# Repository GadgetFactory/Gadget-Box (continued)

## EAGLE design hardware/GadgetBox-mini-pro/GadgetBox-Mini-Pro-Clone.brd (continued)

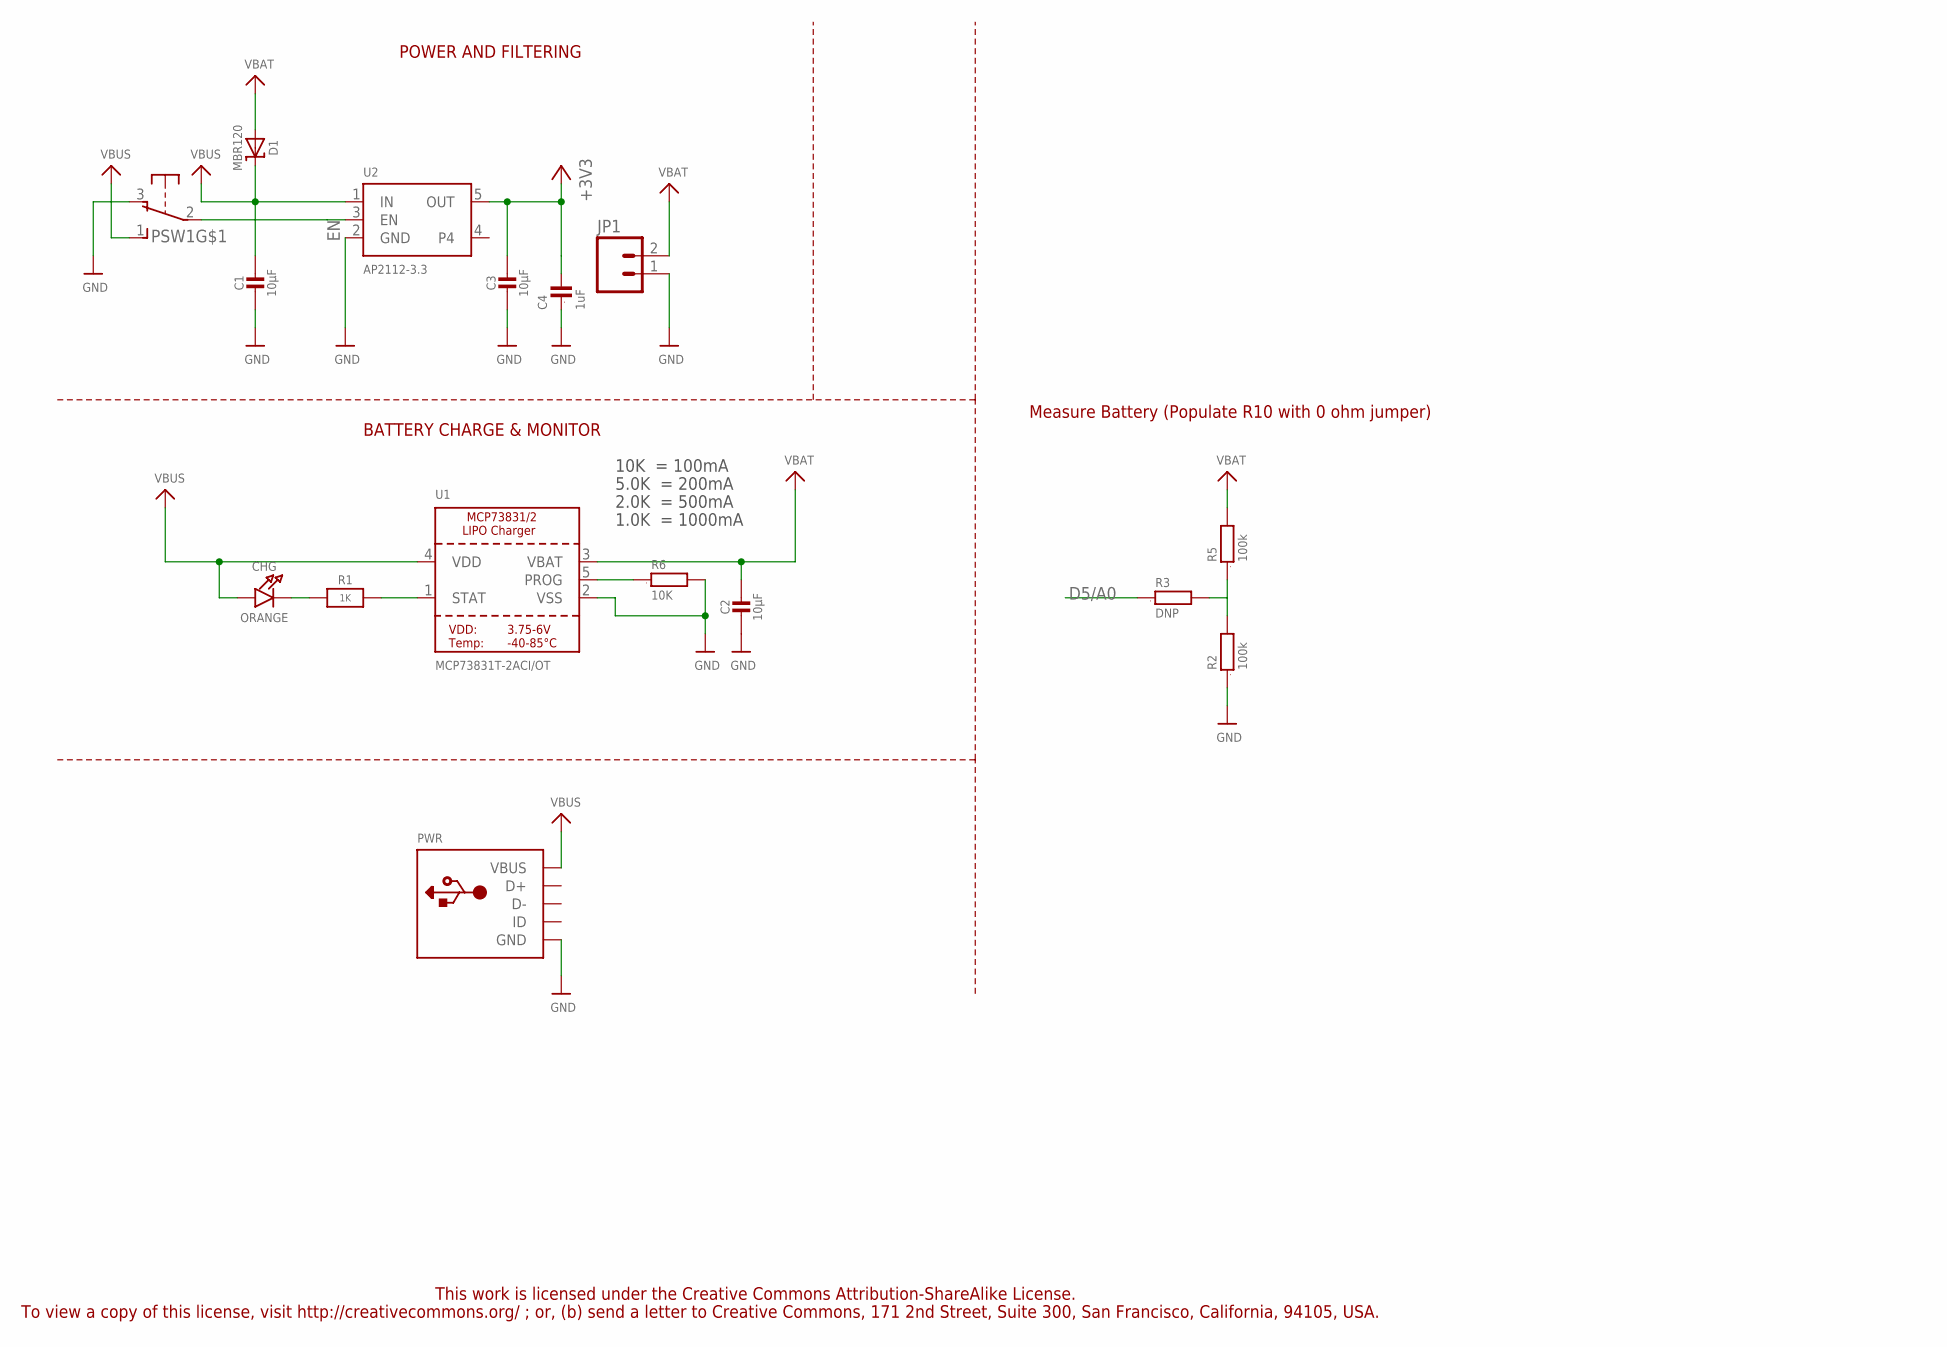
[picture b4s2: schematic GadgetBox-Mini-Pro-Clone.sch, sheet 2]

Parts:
C1, C2, C3: 10µF; 0805-NO; PARTNO CL21F106ZPFNNNE,Samsung,DK,1276-3012-1-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
C4: 1uF; 0603; PARTNO C1608X5R1A105K080AC,TDK CORPORATION (VA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
CHG: ORANGE; CHIPLED_0805_NOOUTLINE; PARTNO LTST-C171EKT,LITE-ON INC (VA),DK,160-14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
D1: MBR120; SOD-123; PARTNO MBR120VLSFT3G,on semiconductor,dk,MBR12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
JP1: M02-JST-2-PTH-NO_SILK; JST-2-PTH-NS; PARTNO B2B-PH-SM4-TB(LF)(SN),JST SALES AMERICA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
PSW1: OS102011MA1Q; PARTNO OS102011MA1QN1,C&K Components,dk,CKN955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
PWR: USBMINIB; USB-MINIB; PARTNO USB-M26FTR,On Shore Technology Inc,DK,E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
R1: 1K; 0603-NO; PARTNO RC0603JR-071KL,YAGEO (VA),dk,311-1.0KGR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
R2, R5: 100k; 0603; PARTNO RC0603JR-07100KL,YAGEO (VA),dk,311-100K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
R3: DNP; 0603
R6: 10K; 0603; PARTNO RC0603JR-0710KL,YAGEO (VA),dk,311-10KGR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
U1: MCP73831T-2ACI/OT; SOT23-5; PARTNO MCP73831T-2ACI/OT,MICROCHIP TECHNOLOGY 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
U2: AP2112-3.3; SOT23-5; PARTNO AP2112K-3.3TRG1,Diodes Incorporated,dk,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

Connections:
3V3: C3.1, C4.2, U2.5 (OUT); also elsewhere on the board
5V0: C1.1, CHG.A, D1.C, PSW1.1 (S), PWR.VBUS, U1.4 (VDD), U2.1 (IN); also elsewhere on the board
D5/A0: R3.1; also elsewhere on the board
EN: PSW1.2, U2.3 (EN)
GND: C1.2, C2.2, C3.2, C4.1, JP1.1, PSW1.3 (O), PWR.GND, R2.1, R6.2, U1.2 (VSS), U2.2 (GND); also elsewhere on the board
unnamed: CHG.C, R1.1
unnamed: R2.2, R3.2, R5.1
unnamed: R1.2, U1.1 (STAT)
unnamed: R6.1, U1.5 (PROG)
VBAT: C2.1, D1.A, JP1.2, R5.2, U1.3 (VBAT)

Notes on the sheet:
POWER AND FILTERING
10K = 100mA
5.0K = 200mA
2.0K = 500mA
1.0K = 1000mA
BATTERY CHARGE & MONITOR
Measure Battery (Populate R10 with 0 ohm jumper)
This work is licensed under the Creative Commons Attribution-ShareAlike License.
To view a copy of this license, visit http://creativecommons.org/ ; or, (b) send a letter to Creative Commons, 171 2nd Street, Suite 300, San Francisco, California, 94105, USA.

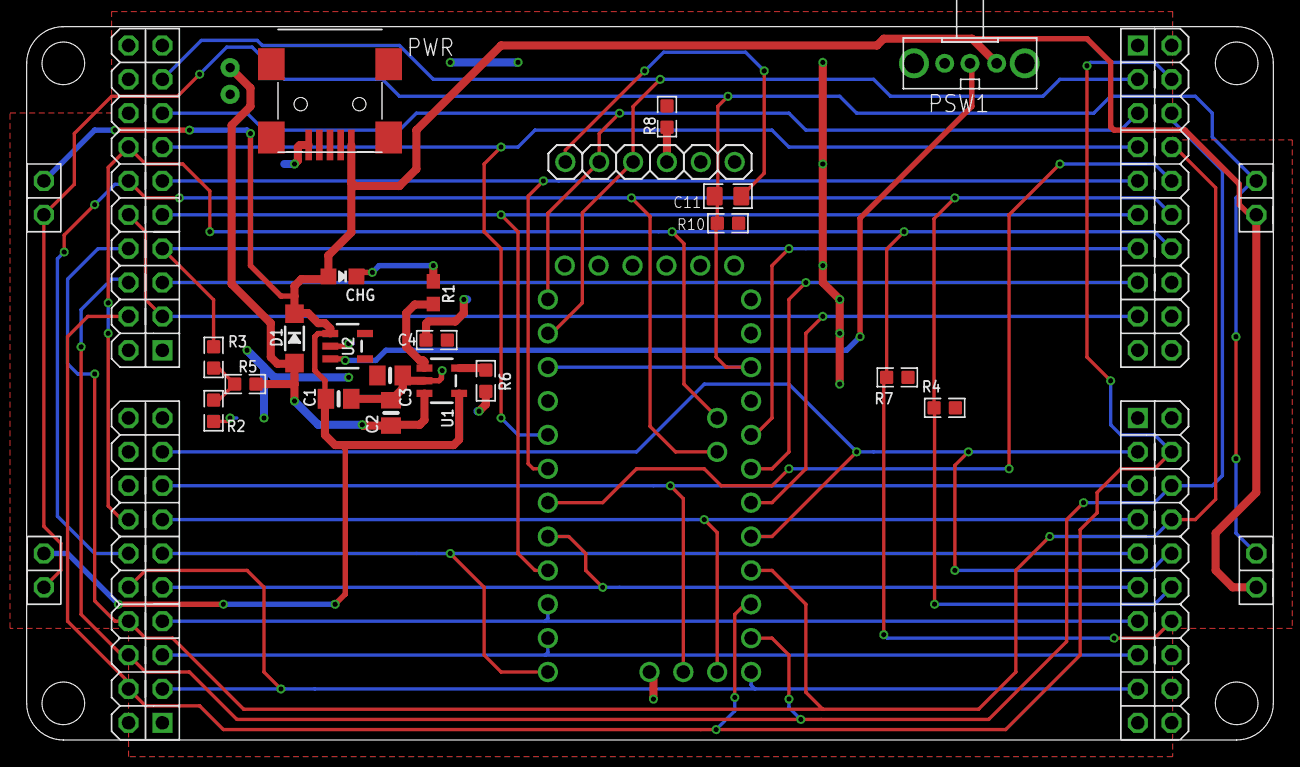
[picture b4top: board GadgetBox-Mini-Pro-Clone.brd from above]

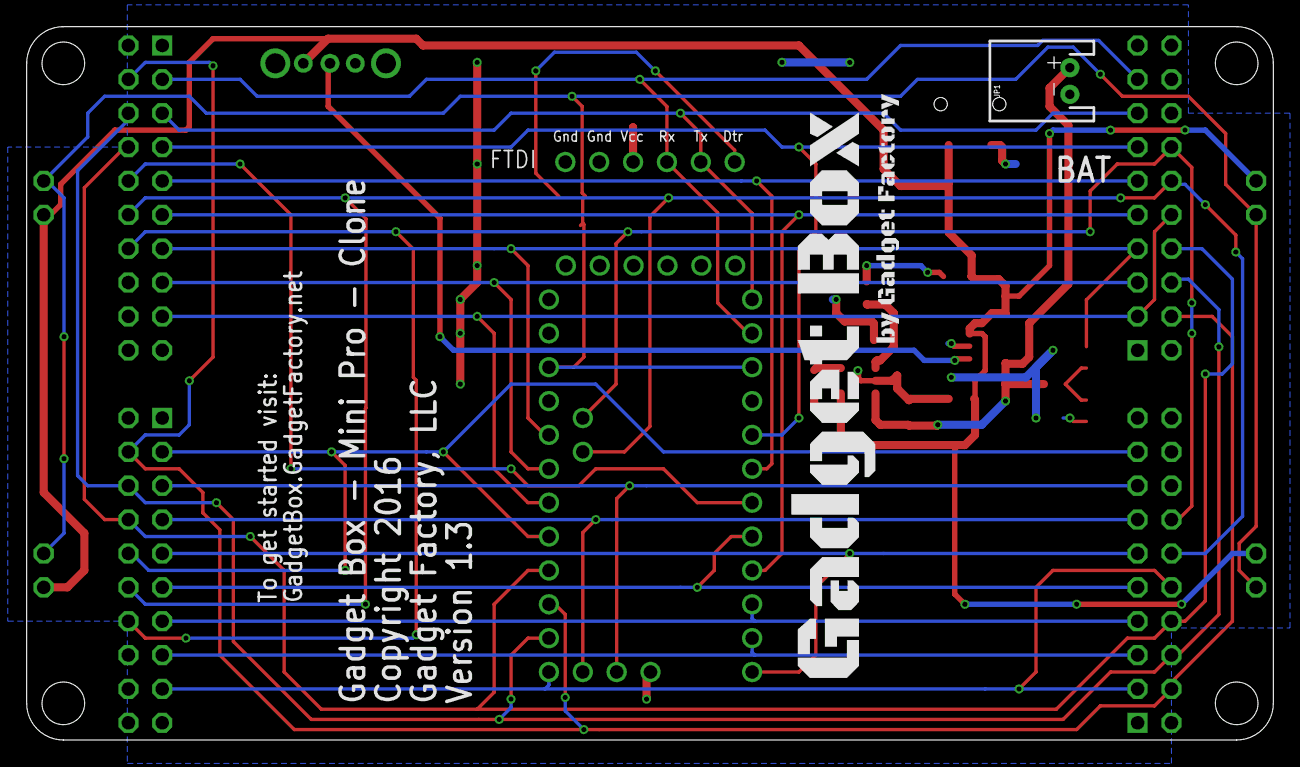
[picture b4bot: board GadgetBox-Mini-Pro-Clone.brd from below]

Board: 2 copper layers, 93.5 x 53.5 mm, 29 parts (2 on the bottom side), 34 nets.

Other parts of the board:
$$U$1: ECOG93P53P5
U$100: GADGETBOX_TEXT

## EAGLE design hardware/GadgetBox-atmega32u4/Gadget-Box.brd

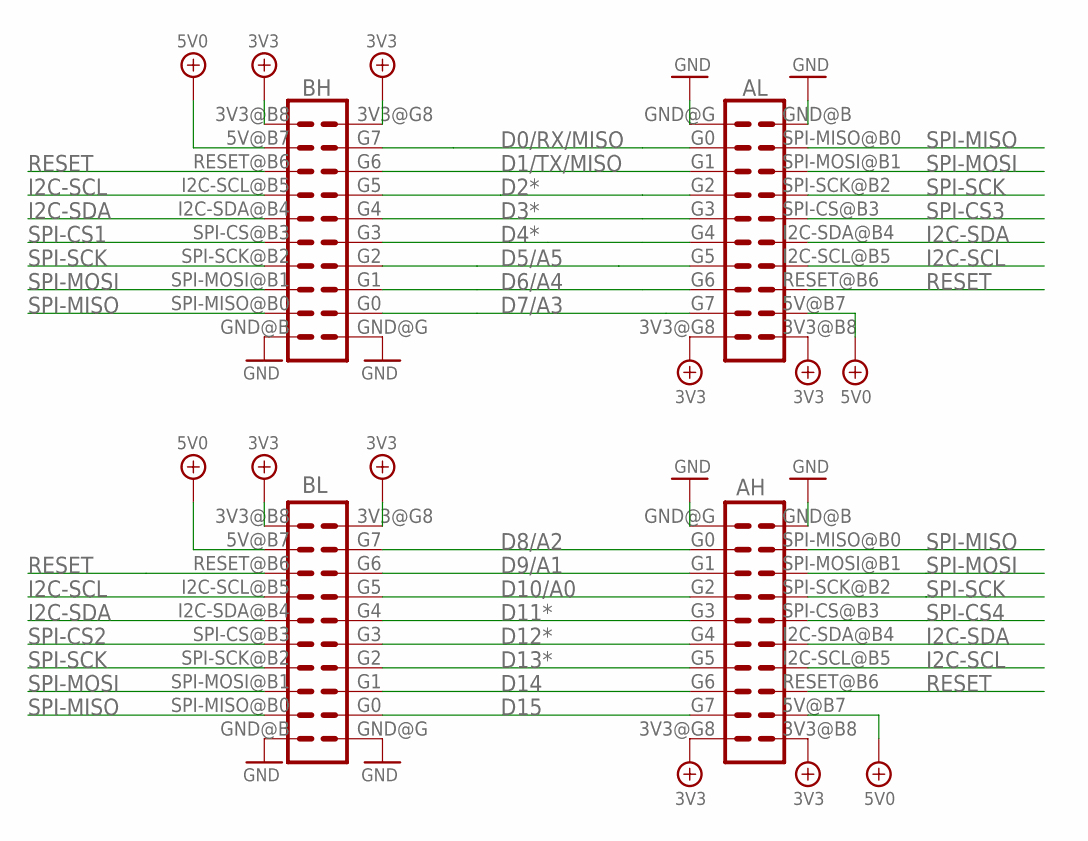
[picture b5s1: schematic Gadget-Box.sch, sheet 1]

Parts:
AH: ECOGECOG_SLOT; ECOG; PARTNO PPPC102LFBN-RC,SULLINS CONNECTOR SOLUTI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
AL: ECOGECOG_SLOT; ECOG; PARTNO PPPC102LFBN-RC,SULLINS CONNECTOR SOLUTI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
BH: ECOGECOG_SLOT; ECOG; PARTNO PPPC102LFBN-RC,SULLINS CONNECTOR SOLUTI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
BL: ECOGECOG_SLOT; ECOG; PARTNO PPPC102LFBN-RC,SULLINS CONNECTOR SOLUTI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

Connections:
3V3: AH.3V3@B8 (3V3), AH.3V3@G8 (3V3), AL.3V3@B8 (3V3), AL.3V3@G8 (3V3), BH.3V3@B8 (3V3), BH.3V3@G8 (3V3), BL.3V3@B8 (3V3), BL.3V3@G8 (3V3); also elsewhere on the board
D0/RX/MISO: AL.G0, BH.G7; also elsewhere on the board
D1/TX/MISO: AL.G1, BH.G6; also elsewhere on the board
D2*: AL.G2, BH.G5; also elsewhere on the board
D3*: AL.G3, BH.G4; also elsewhere on the board
D4*: AL.G4, BH.G3; also elsewhere on the board
D5/A5: AL.G5, BH.G2; also elsewhere on the board
D6/A4: AL.G6, BH.G1; also elsewhere on the board
D7/A3: AL.G7, BH.G0; also elsewhere on the board
D8/A2: AH.G0, BL.G7; also elsewhere on the board
D9/A1: AH.G1, BL.G6; also elsewhere on the board
D10/A0: AH.G2, BL.G5; also elsewhere on the board
D11*: AH.G3, BL.G4; also elsewhere on the board
D12*: AH.G4, BL.G3; also elsewhere on the board
D13*: AH.G5, BL.G2; also elsewhere on the board
D14: AH.G6, BL.G1; also elsewhere on the board
D15: AH.G7, BL.G0; also elsewhere on the board
GND: AH.GND@B (GND), AH.GND@G (GND), AL.GND@B (GND), AL.GND@G (GND), BH.GND@B (GND), BH.GND@G (GND), BL.GND@B (GND), BL.GND@G (GND); also elsewhere on the board
I2C-SCL: AH.I2C-SCL@B5 (I2C-SCL), AL.I2C-SCL@B5 (I2C-SCL), BH.I2C-SCL@B5 (I2C-SCL), BL.I2C-SCL@B5 (I2C-SCL); also elsewhere on the board
I2C-SDA: AH.I2C-SDA@B4 (I2C-SDA), AL.I2C-SDA@B4 (I2C-SDA), BH.I2C-SDA@B4 (I2C-SDA), BL.I2C-SDA@B4 (I2C-SDA); also elsewhere on the board
RESET: AH.RESET@B6 (RESET), AL.RESET@B6 (RESET), BH.RESET@B6 (RESET), BL.RESET@B6 (RESET); also elsewhere on the board
SPI-CS1: BH.SPI-CS@B3 (SPI-CS); also elsewhere on the board
SPI-CS2: BL.SPI-CS@B3 (SPI-CS); also elsewhere on the board
SPI-CS3: AL.SPI-CS@B3 (SPI-CS); also elsewhere on the board
SPI-CS4: AH.SPI-CS@B3 (SPI-CS); also elsewhere on the board
SPI-MISO: AH.SPI-MISO@B0 (SPI-MISO), AL.SPI-MISO@B0 (SPI-MISO), BH.SPI-MISO@B0 (SPI-MISO), BL.SPI-MISO@B0 (SPI-MISO); also elsewhere on the board
SPI-MOSI: AH.SPI-MOSI@B1 (SPI-MOSI), AL.SPI-MOSI@B1 (SPI-MOSI), BH.SPI-MOSI@B1 (SPI-MOSI), BL.SPI-MOSI@B1 (SPI-MOSI); also elsewhere on the board
SPI-SCK: AH.SPI-SCK@B2 (SPI-SCK), AL.SPI-SCK@B2 (SPI-SCK), BH.SPI-SCK@B2 (SPI-SCK), BL.SPI-SCK@B2 (SPI-SCK); also elsewhere on the board
VBUS: AH.5V@B7 (5V), AL.5V@B7 (5V), BH.5V@B7 (5V), BL.5V@B7 (5V); also elsewhere on the board

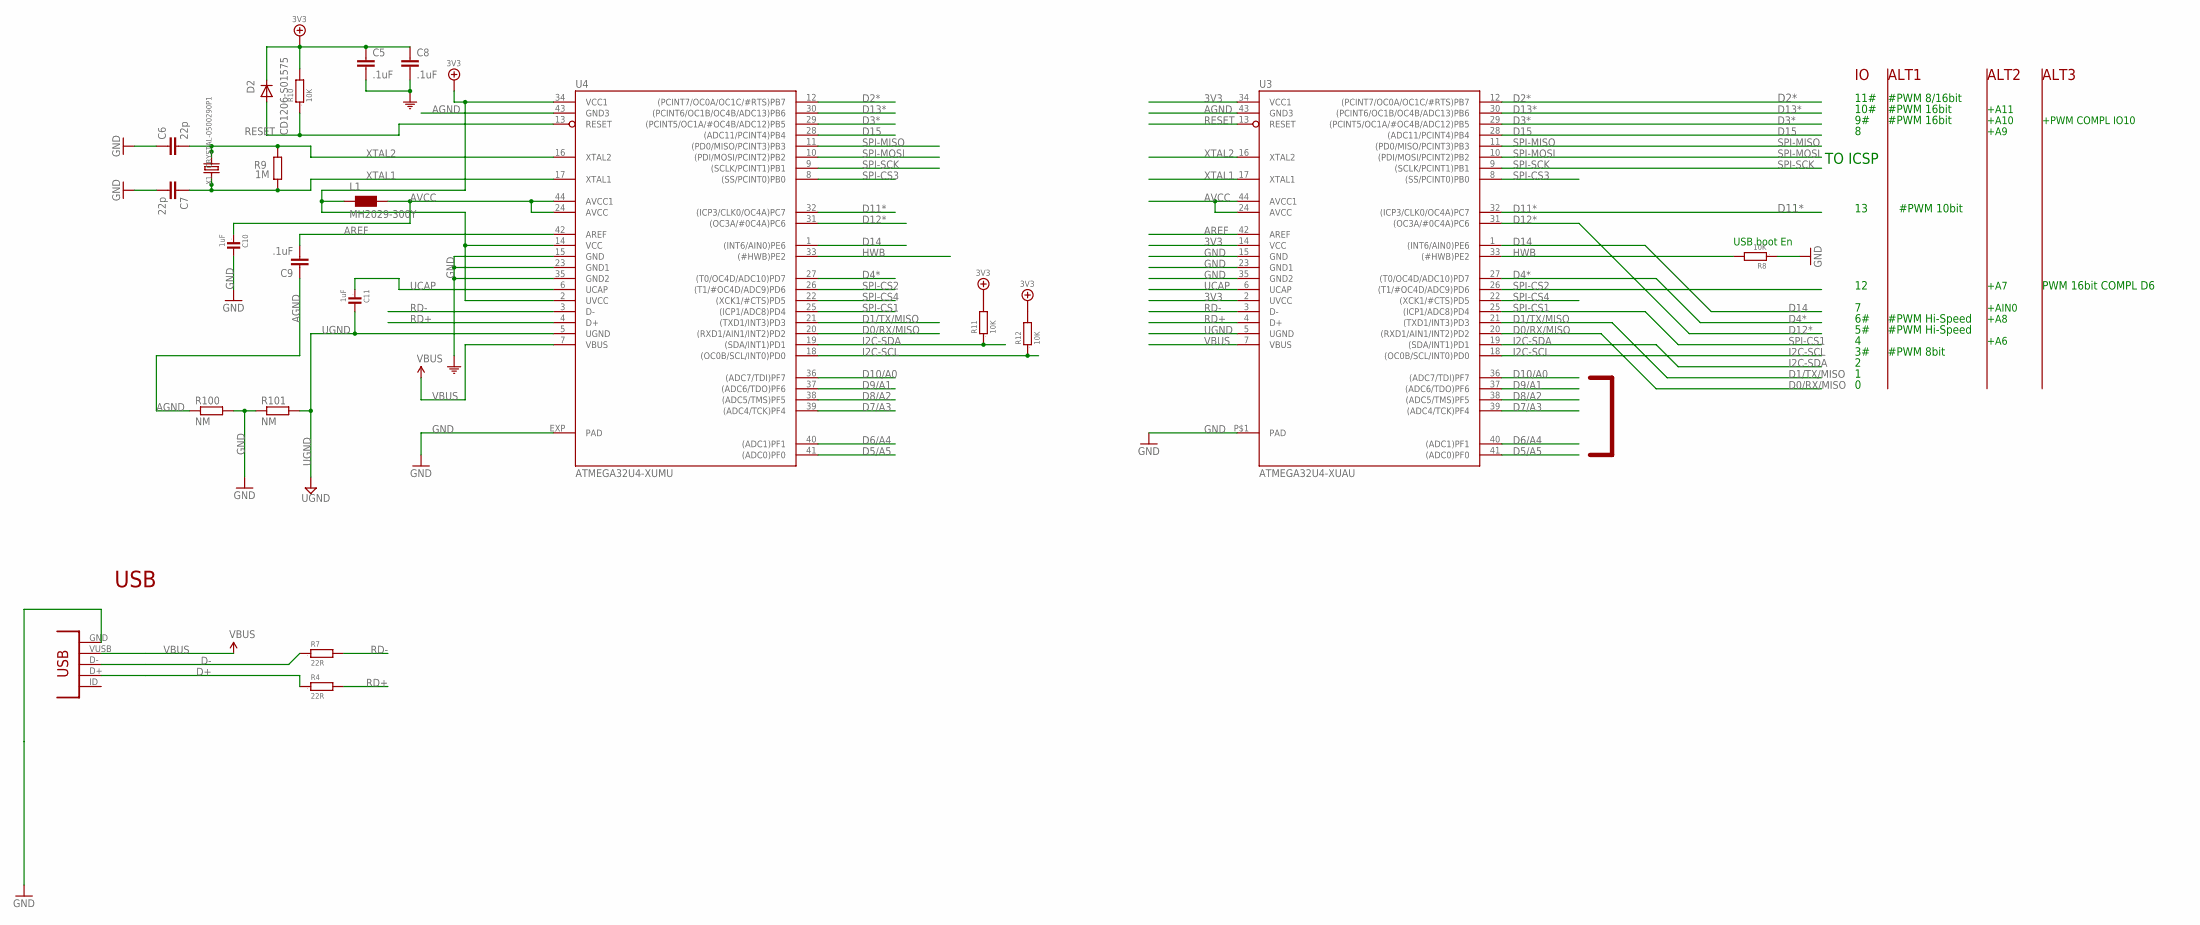
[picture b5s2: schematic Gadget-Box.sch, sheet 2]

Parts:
C5, C8, C9: .1uF; C0603-ROUND; PARTNO GRM188F51E104ZA01D,MURATA ELECTRONICS (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
C6, C7: 22p; C0603-ROUND; PARTNO C1608C0G1H220J080AA,TDK CORPORATION (VA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
C10, C11: 1uF; 0603; PARTNO C1608X5R1A105K080AC,TDK CORPORATION (VA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
D2: CD1206-S01575; MINIMELF; PARTNO CD1206-S01575,BOURNS INC (VA),dk,CD1206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
L1: MH2029-300Y; 0805; PARTNO MH2029-300Y,BOURNS INC (VA),dk,MH2029-3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
R4, R7: 22R; 0805; PARTNO RMCF0805JT22R0,STACKPOLE ELECTRONICS IN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
R8, R10, R11, R12: 10K; 0603; PARTNO RC0603JR-0710KL,YAGEO (VA),dk,311-10KGR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
R9: 1M; R0603-ROUND; PARTNO RMCF0603JT1M00,STACKPOLE ELECTRONICS IN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
R100, R101: NM; R0402
U3: ATMEGA32U4-XUAU; TQFP44-PAD; PARTNO ATMEGA32U4-AUR,ATMEL (VA),dk,ATMEGA32U4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
U4: ATMEGA32U4-XUMU; QFN44ML7X7
USB: CONN_USB; CONN_USB_MINI-B; PARTNO USB-M26FTR,ON SHORE TECHNOLOGY INC (VA)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
X1: CRYSTAL-0500290P1; 2P-SMD-5.0X3.2; PARTNO ABM3-8.000MHZ-D2Y-T,Abracon Corporation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

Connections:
3V3: C5.1, C8.1, D2.C, L1.1, R10.2, R11.2, R12.2, U3.2 (UVCC), U3.14 (VCC), U3.34 (VCC1), U4.2 (UVCC), U4.14 (VCC), U4.34 (VCC1); also elsewhere on the board
AGND: C9.1, R100.1, U3.43 (GND3), U4.43 (GND3)
AREF: C9.2, U3.42 (AREF), U4.42 (AREF)
AVCC: C10.1, L1.2, U3.24 (AVCC), U3.44 (AVCC1), U4.24 (AVCC), U4.44 (AVCC1)
D0/RX/MISO: U3.20 ((RXD1/AIN1/INT2)PD2), U4.20 ((RXD1/AIN1/INT2)PD2); also elsewhere on the board
D1/TX/MISO: U3.21 ((TXD1/INT3)PD3), U4.21 ((TXD1/INT3)PD3); also elsewhere on the board
D2*: U3.12 ((PCINT7/OC0A/OC1C/#RTS)PB7), U4.12 ((PCINT7/OC0A/OC1C/#RTS)PB7); also elsewhere on the board
D3*: U3.29 ((PCINT5/OC1A/#OC4B/ADC12)PB5), U4.29 ((PCINT5/OC1A/#OC4B/ADC12)PB5); also elsewhere on the board
D4*: U3.27 ((T0/OC4D/ADC10)PD7), U4.27 ((T0/OC4D/ADC10)PD7); also elsewhere on the board
D5/A5: U3.41 ((ADC0)PF0), U4.41 ((ADC0)PF0); also elsewhere on the board
D6/A4: U3.40 ((ADC1)PF1), U4.40 ((ADC1)PF1); also elsewhere on the board
D7/A3: U3.39 ((ADC4/TCK)PF4), U4.39 ((ADC4/TCK)PF4); also elsewhere on the board
D8/A2: U3.38 ((ADC5/TMS)PF5), U4.38 ((ADC5/TMS)PF5); also elsewhere on the board
D9/A1: U3.37 ((ADC6/TDO)PF6), U4.37 ((ADC6/TDO)PF6); also elsewhere on the board
D10/A0: U3.36 ((ADC7/TDI)PF7), U4.36 ((ADC7/TDI)PF7); also elsewhere on the board
D11*: U3.32 ((ICP3/CLK0/OC4A)PC7), U4.32 ((ICP3/CLK0/OC4A)PC7); also elsewhere on the board
D12*: U3.31 ((OC3A/#0C4A)PC6), U4.31 ((OC3A/#0C4A)PC6); also elsewhere on the board
D13*: U3.30 ((PCINT6/OC1B/OC4B/ADC13)PB6), U4.30 ((PCINT6/OC1B/OC4B/ADC13)PB6); also elsewhere on the board
D14: U3.1 ((INT6/AIN0)PE6), U4.1 ((INT6/AIN0)PE6); also elsewhere on the board
D15: U3.28 ((ADC11/PCINT4)PB4), U4.28 ((ADC11/PCINT4)PB4); also elsewhere on the board
D+: R4.1, USB.D+
D-: R7.1, USB.D-
GND: C5.2, C6.1, C7.2, C8.2, C10.2, R8.1, R100.2, R101.1, U3.15 (GND), U3.23 (GND1), U3.35 (GND2), U3.P$1 (PAD), U4.15 (GND), U4.23 (GND1), U4.35 (GND2), U4.EXP (PAD), USB.GND; also elsewhere on the board
HWB: R8.2, U3.33 ((#HWB)PE2), U4.33 ((#HWB)PE2)
I2C-SCL: R12.1, U3.18 ((OC0B/SCL/INT0)PD0), U4.18 ((OC0B/SCL/INT0)PD0); also elsewhere on the board
I2C-SDA: R11.1, U3.19 ((SDA/INT1)PD1), U4.19 ((SDA/INT1)PD1); also elsewhere on the board
RD+: R4.2, U3.4 (D+), U4.4 (D+)
RD-: R7.2, U3.3 (D-), U4.3 (D-)
RESET: D2.A, R10.1, U3.13 (RESET), U4.13 (RESET); also elsewhere on the board
SPI-CS1: U3.25 ((ICP1/ADC8)PD4), U4.25 ((ICP1/ADC8)PD4); also elsewhere on the board
SPI-CS2: U3.26 ((T1/#OC4D/ADC9)PD6), U4.26 ((T1/#OC4D/ADC9)PD6); also elsewhere on the board
SPI-CS3: U3.8 ((SS/PCINT0)PB0), U4.8 ((SS/PCINT0)PB0); also elsewhere on the board
SPI-CS4: U3.22 ((XCK1/#CTS)PD5), U4.22 ((XCK1/#CTS)PD5); also elsewhere on the board
SPI-MISO: U3.11 ((PD0/MISO/PCINT3)PB3), U4.11 ((PD0/MISO/PCINT3)PB3); also elsewhere on the board
SPI-MOSI: U3.10 ((PDI/MOSI/PCINT2)PB2), U4.10 ((PDI/MOSI/PCINT2)PB2); also elsewhere on the board
SPI-SCK: U3.9 ((SCLK/PCINT1)PB1), U4.9 ((SCLK/PCINT1)PB1); also elsewhere on the board
UCAP: C11.1, U3.6 (UCAP), U4.6 (UCAP)
UGND: C11.2, R101.2, U3.5 (UGND), U4.5 (UGND)
VBUS: U3.7 (VBUS), U4.7 (VBUS), USB.VUSB; also elsewhere on the board
XTAL1: C7.1, R9.1, U3.17 (XTAL1), U4.17 (XTAL1), X1.1
XTAL2: C6.2, R9.2, U3.16 (XTAL2), U4.16 (XTAL2), X1.2

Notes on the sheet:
USB boot En
USB
TO ICSP
10#
11#
#PWM 8bit
#PWM Hi-Speed
#PWM 8/16bit
#PWM 16bit
PWM 16bit COMPL D6
#PWM 10bit
+A6
+A7
+A11
+A10
+A8
+A9
+PWM COMPL IO10
+AIN0
ALT1
ALT2
ALT3

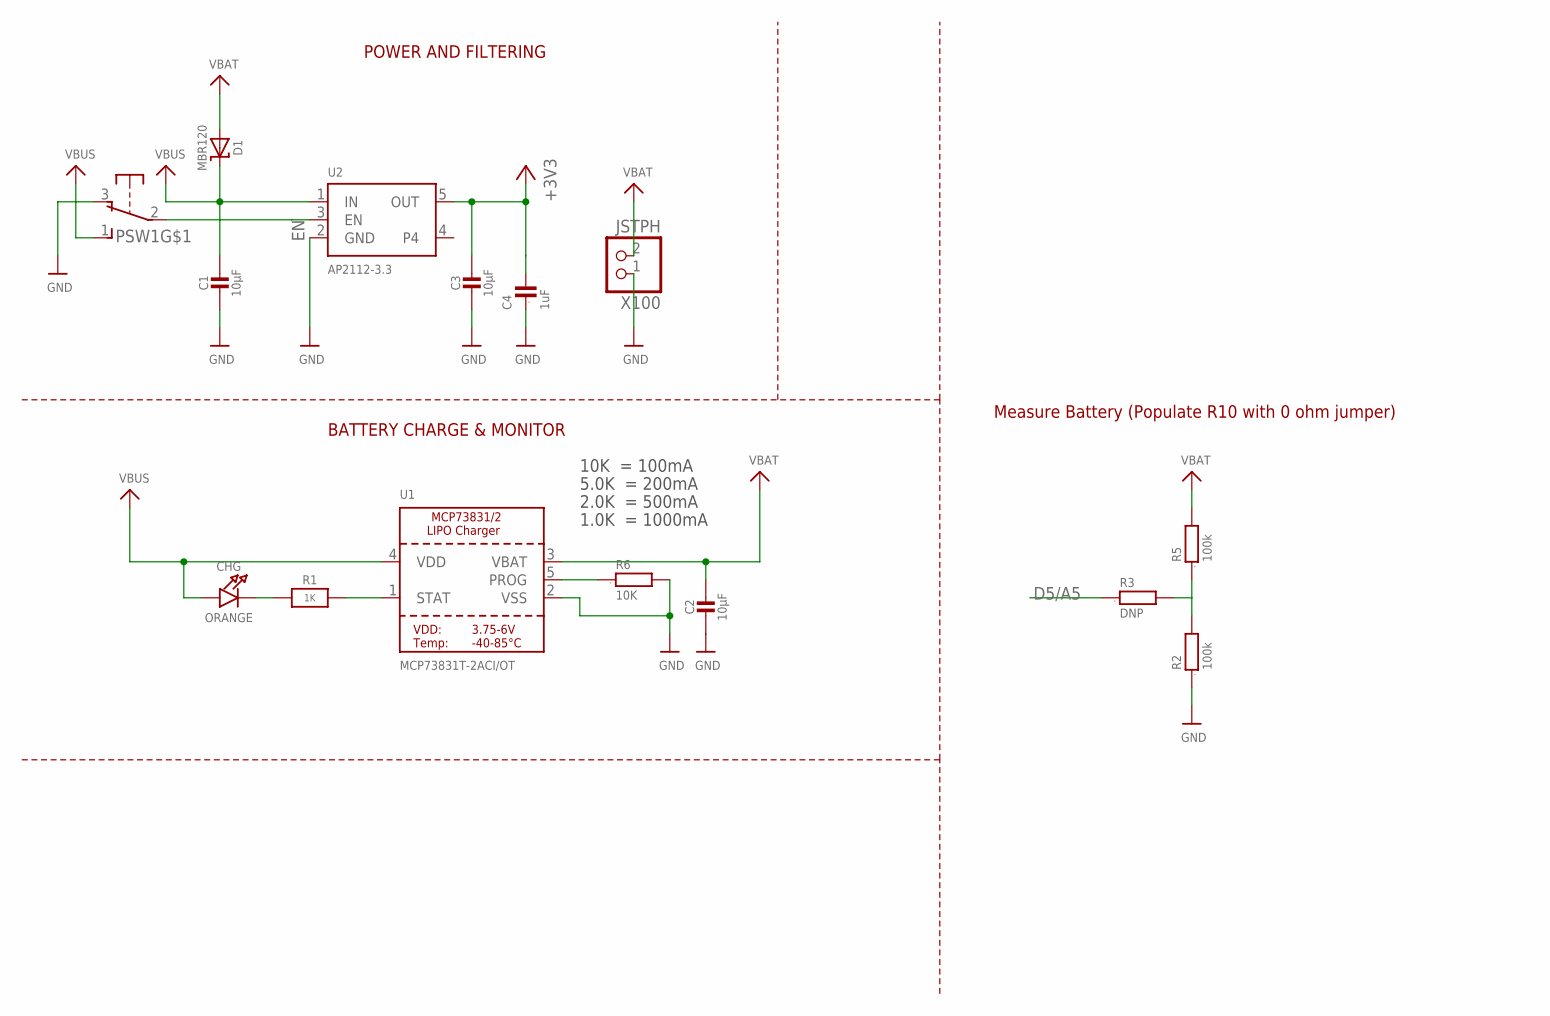
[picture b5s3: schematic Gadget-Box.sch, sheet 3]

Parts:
C1, C2, C3: 10µF; 0805-NO; PARTNO CL21F106ZPFNNNE,Samsung,DK,1276-3012-1-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
C4: 1uF; 0603; PARTNO C1608X5R1A105K080AC,TDK CORPORATION (VA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
CHG: ORANGE; CHIPLED_0805_NOOUTLINE; PARTNO LTST-C171EKT,LITE-ON INC (VA),DK,160-14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
D1: MBR120; SOD-123; PARTNO MBR120VLSFT3G,on semiconductor,dk,MBR12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
PSW1: OS102011MA1Q; PARTNO OS102011MA1QN1,C&K Components,dk,CKN955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
R1: 1K; 0603-NO; PARTNO RC0603JR-071KL,YAGEO (VA),dk,311-1.0KGR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
R2, R5: 100k; 0603; PARTNO RC0603JR-07100KL,YAGEO (VA),dk,311-100K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
R3: DNP; 0603
R6: 10K; 0603; PARTNO RC0603JR-0710KL,YAGEO (VA),dk,311-10KGR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
U1: MCP73831T-2ACI/OT; SOT23-5; PARTNO MCP73831T-2ACI/OT,MICROCHIP TECHNOLOGY 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
U2: AP2112-3.3; SOT23-5; PARTNO AP2112K-3.3TRG1,Diodes Incorporated,dk,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
X100: JSTPH; JSTPH2; PARTNO S2B-PH-SM4-TB(LF)(SN),JST SALES AMERICA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

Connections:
3V3: C3.1, C4.2, U2.5 (OUT); also elsewhere on the board
D5/A5: R3.1; also elsewhere on the board
EN: PSW1.2, U2.3 (EN)
GND: C1.2, C2.2, C3.2, C4.1, PSW1.3 (O), R2.1, R6.2, U1.2 (VSS), U2.2 (GND), X100.1; also elsewhere on the board
unnamed: CHG.C, R1.1
unnamed: R2.2, R3.2, R5.1
unnamed: R1.2, U1.1 (STAT)
unnamed: R6.1, U1.5 (PROG)
VBAT: C2.1, D1.A, R5.2, U1.3 (VBAT), X100.2
VBUS: C1.1, CHG.A, D1.C, PSW1.1 (S), U1.4 (VDD), U2.1 (IN); also elsewhere on the board

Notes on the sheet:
POWER AND FILTERING
10K = 100mA
5.0K = 200mA
2.0K = 500mA
1.0K = 1000mA
BATTERY CHARGE & MONITOR
Measure Battery (Populate R10 with 0 ohm jumper)

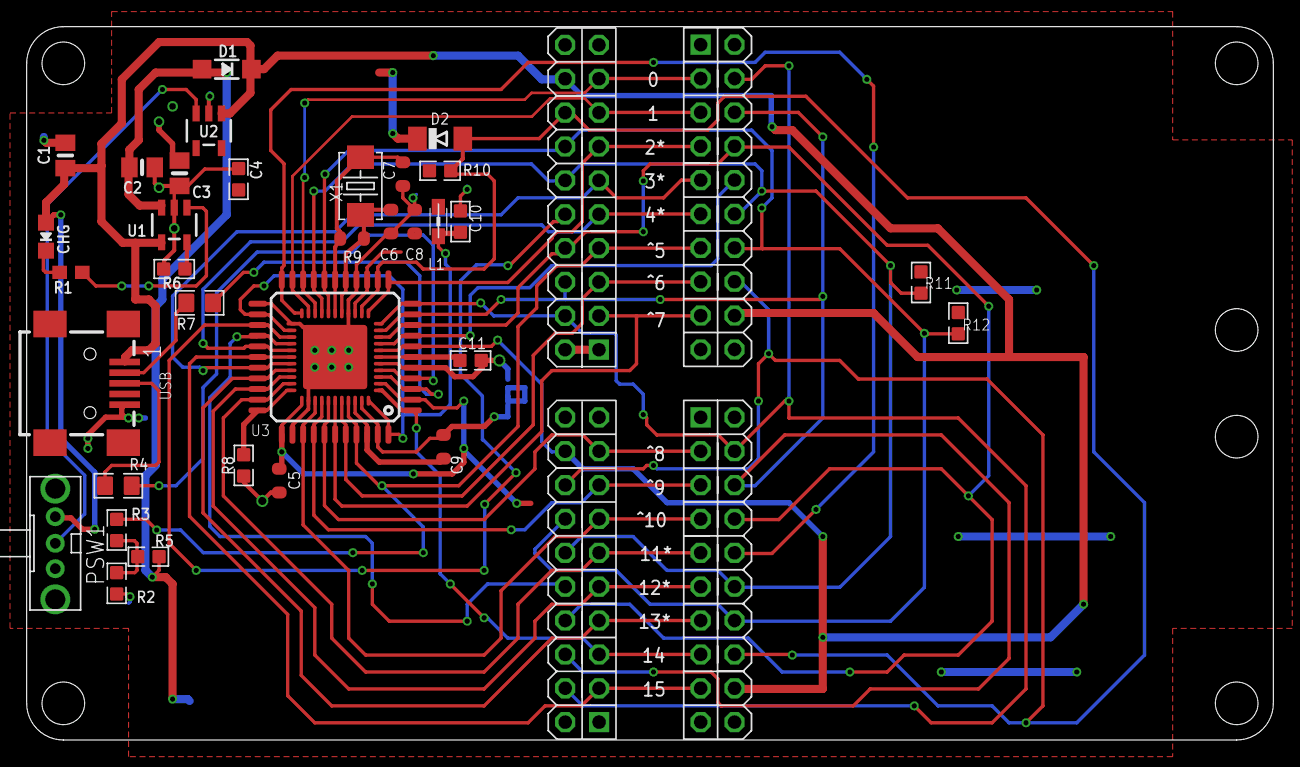
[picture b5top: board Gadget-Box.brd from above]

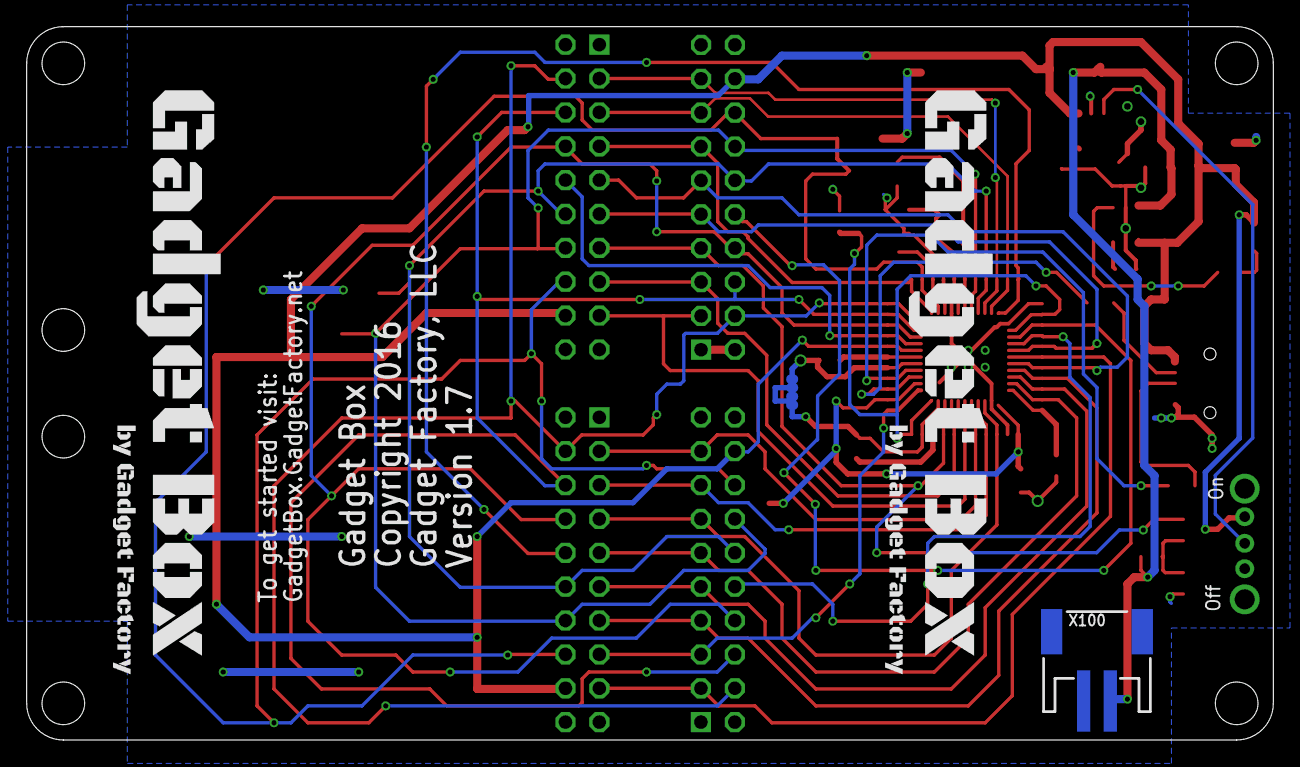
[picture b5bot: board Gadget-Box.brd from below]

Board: 2 copper layers, 93.5 x 53.5 mm, 44 parts (5 on the bottom side), 47 nets.

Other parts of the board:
$$U$1: ECOG93P53P5
U$100, U$101: GADGETBOX_TEXT

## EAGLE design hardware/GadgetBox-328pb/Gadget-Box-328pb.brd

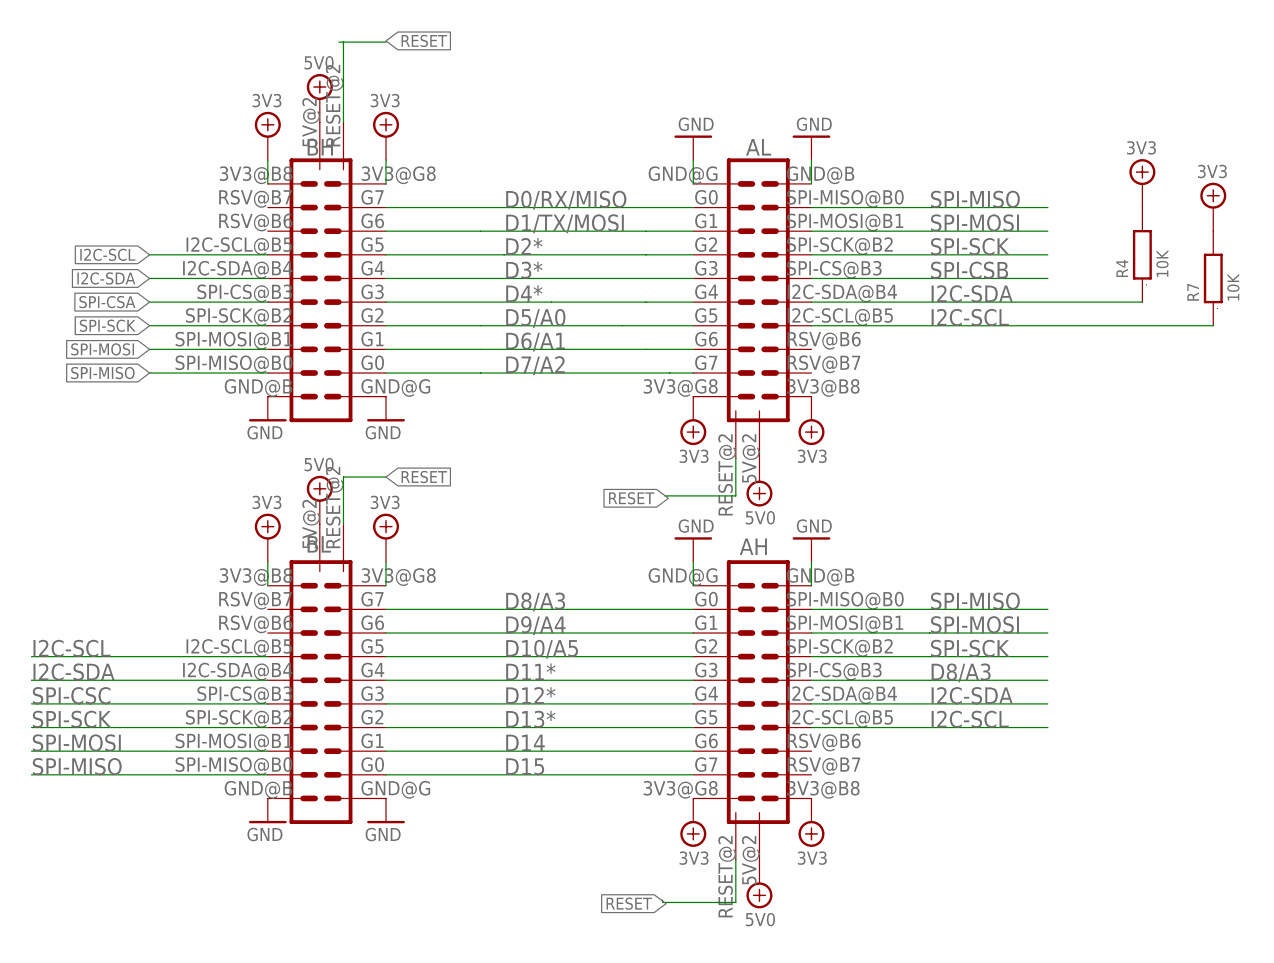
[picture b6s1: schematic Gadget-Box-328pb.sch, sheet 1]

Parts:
AH: ECOGECOG_SLOT_ALT1; ECOG_ALT1; PARTNO PPPC102LFBN-RC,SULLINS CONNECTOR SOLUTI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
AL: ECOGECOG_SLOT_ALT1; ECOG_ALT1; PARTNO PPPC102LFBN-RC,SULLINS CONNECTOR SOLUTI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
BH: ECOGECOG_SLOT_ALT1; ECOG_ALT1; PARTNO PPPC102LFBN-RC,SULLINS CONNECTOR SOLUTI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
BL: ECOGECOG_SLOT_ALT1; ECOG_ALT1; PARTNO PPPC102LFBN-RC,SULLINS CONNECTOR SOLUTI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
R4, R7: 10K; 0603; PARTNO RC0603JR-0710KL,YAGEO (VA),dk,311-10KGR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

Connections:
3V3: AH.3V3@B8 (3V3), AH.3V3@G8 (3V3), AL.3V3@B8 (3V3), AL.3V3@G8 (3V3), BH.3V3@B8 (3V3), BH.3V3@G8 (3V3), BL.3V3@B8 (3V3), BL.3V3@G8 (3V3), R4.2, R7.2; also elsewhere on the board
5V0: AH.5V@2 (5V), AL.5V@2 (5V), BH.5V@2 (5V), BL.5V@2 (5V); also elsewhere on the board
D0/RX/MISO: AL.G0, BH.G7; also elsewhere on the board
D1/TX/MOSI: AL.G1, BH.G6; also elsewhere on the board
D2*: AL.G2, BH.G5; also elsewhere on the board
D3*: AL.G3, BH.G4; also elsewhere on the board
D4*: AL.G4, BH.G3; also elsewhere on the board
D5/A0: AL.G5, BH.G2; also elsewhere on the board
D6/A1: AL.G6, BH.G1; also elsewhere on the board
D7/A2: AL.G7, BH.G0; also elsewhere on the board
D8/A3: AH.G0, AH.SPI-CS@B3 (SPI-CS), BL.G7; also elsewhere on the board
D9/A4: AH.G1, BL.G6; also elsewhere on the board
D10/A5: AH.G2, BL.G5; also elsewhere on the board
D11*: AH.G3, BL.G4; also elsewhere on the board
D12*: AH.G4, BL.G3; also elsewhere on the board
D13*: AH.G5, BL.G2; also elsewhere on the board
D14: AH.G6, BL.G1; also elsewhere on the board
D15: AH.G7, BL.G0; also elsewhere on the board
GND: AH.GND@B (GND), AH.GND@G (GND), AL.GND@B (GND), AL.GND@G (GND), BH.GND@B (GND), BH.GND@G (GND), BL.GND@B (GND), BL.GND@G (GND); also elsewhere on the board
I2C-SCL: AH.I2C-SCL@B5 (I2C-SCL), AL.I2C-SCL@B5 (I2C-SCL), BH.I2C-SCL@B5 (I2C-SCL), BL.I2C-SCL@B5 (I2C-SCL), R7.1; also elsewhere on the board
I2C-SDA: AH.I2C-SDA@B4 (I2C-SDA), AL.I2C-SDA@B4 (I2C-SDA), BH.I2C-SDA@B4 (I2C-SDA), BL.I2C-SDA@B4 (I2C-SDA), R4.1; also elsewhere on the board
RESET: AH.RESET@2 (RESET), AL.RESET@2 (RESET), BH.RESET@2 (RESET), BL.RESET@2 (RESET); also elsewhere on the board
SPI-CSA: BH.SPI-CS@B3 (SPI-CS); also elsewhere on the board
SPI-CSB: AL.SPI-CS@B3 (SPI-CS); also elsewhere on the board
SPI-CSC: BL.SPI-CS@B3 (SPI-CS); also elsewhere on the board
SPI-MISO: AH.SPI-MISO@B0 (SPI-MISO), AL.SPI-MISO@B0 (SPI-MISO), BH.SPI-MISO@B0 (SPI-MISO), BL.SPI-MISO@B0 (SPI-MISO); also elsewhere on the board
SPI-MOSI: AH.SPI-MOSI@B1 (SPI-MOSI), AL.SPI-MOSI@B1 (SPI-MOSI), BH.SPI-MOSI@B1 (SPI-MOSI), BL.SPI-MOSI@B1 (SPI-MOSI); also elsewhere on the board
SPI-SCK: AH.SPI-SCK@B2 (SPI-SCK), AL.SPI-SCK@B2 (SPI-SCK), BH.SPI-SCK@B2 (SPI-SCK), BL.SPI-SCK@B2 (SPI-SCK); also elsewhere on the board
